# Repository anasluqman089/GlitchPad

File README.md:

# GlitchPad

It is inspire by the movie Matrix 

Matrix rain on a tiny screen, buttons that trigger glitches and sirens, and a real weather sensor hiding inside.

# BOM

1x Seeed Studio XIAO ESP32-S3

4x Cherry MX keyboard

1x Buzzer

1x 220uf resistor

1x LED

1x Rotary Encoder

1x BME280 breakout board

1x O.91 0LED Screen (Blue)

4x M2 screw

4x M3 screw

# Functions

When you turn it on,

It pretends to "boot up" like the Matrix movie and show the text "WAKE UP, NEO..." on the screen with glitchy beeps

When idle,

The screen shows falling Matrix-style rain and every few seconds your room temperature/humidity flickers inside it.

The 4 buttons

1	- Shows "WAKE UP, NEO... THE MATRIX HAS YOU"

2 -	Glitch attack — screen goes crazy + static noise

3 -	Shows real sensor data (temp, humidity, pressure)

4	- Flashing alarm "SYSTEM BREACH" + siren 

The knob

Turn it - adjusts LED brightness

Click it - makes the Matrix rain fall faster

# The Schematic

# The PCB

# The 3D Model

The full model

The lid

The body

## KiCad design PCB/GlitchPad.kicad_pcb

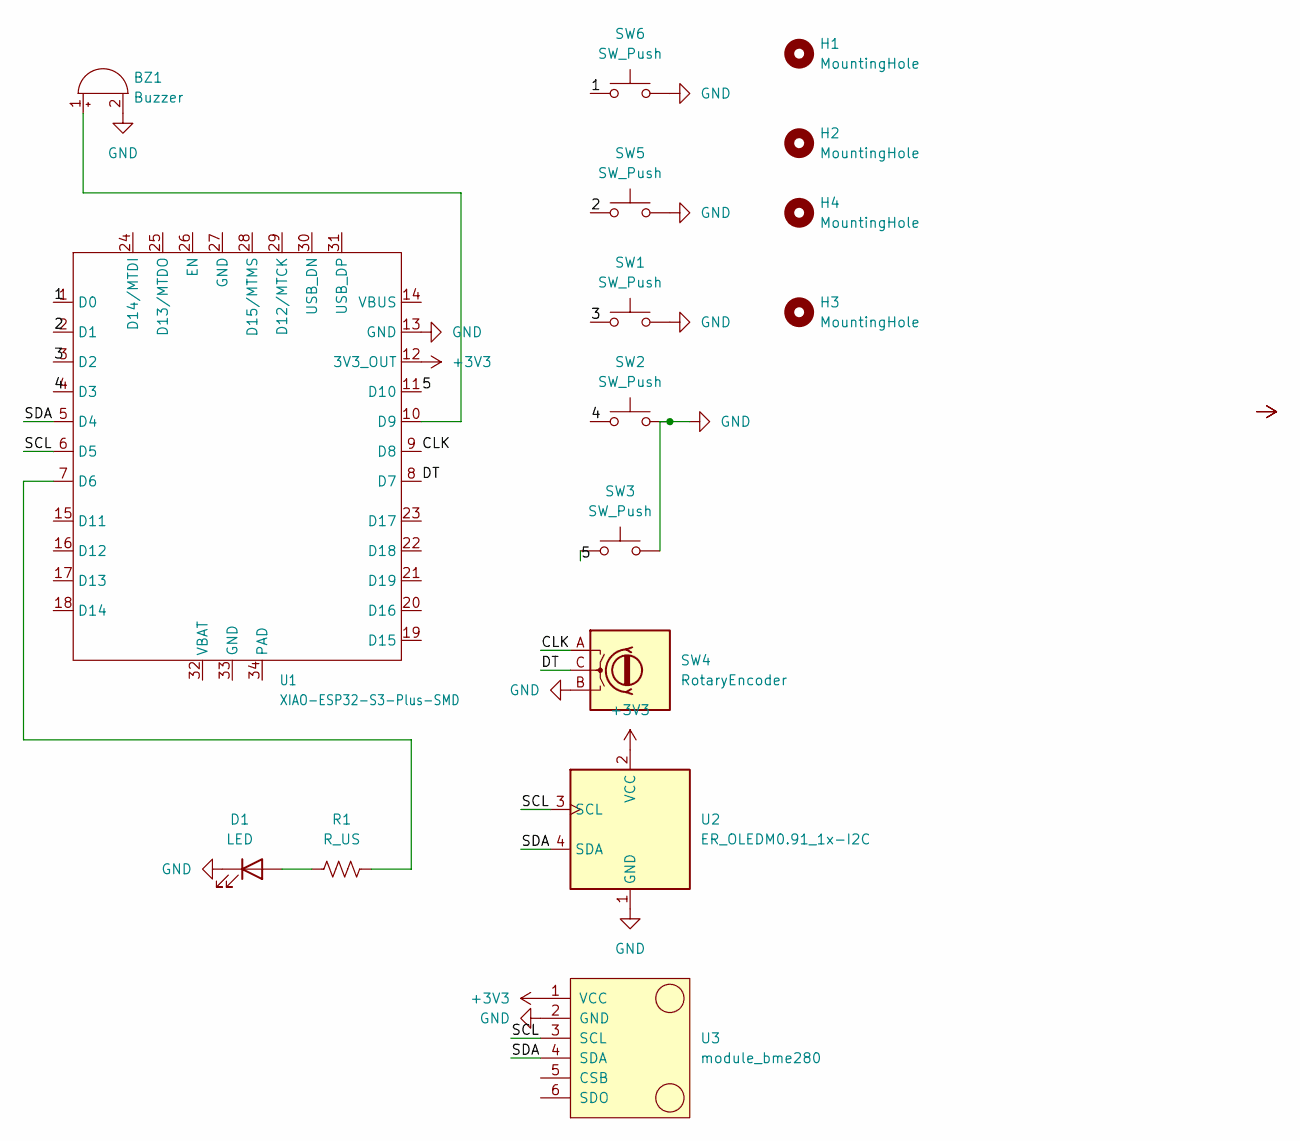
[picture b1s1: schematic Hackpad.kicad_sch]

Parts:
BZ1: Buzzer; Buzzer_12x9.5RM7.6
D1: LED; LED_D5.0mm
H1, H2, H3, H4: MountingHole; MountingHole_2.2mm_M2
R1: R_US; R_Axial_DIN0207_L6.3mm_D2.5mm_P7.62mm_Horizontal
SW1, SW2, SW3, SW5, SW6: SW_Push; SW_Cherry_MX_1.00u_PCB
SW4: RotaryEncoder; RotaryEncoder_Alps_EC11E_Vertical_H20mm
U1: XIAO-ESP32-S3-Plus-SMD; XIAO-ESP32-S3-DIP
U2: ER_OLEDM0.91_1x-I2C
U3: module_bme280

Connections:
+3V3: U1.12 (3V3_OUT), U2.2 (VCC), U3.1 (VCC)
/1: SW6.1, U1.1 (D0)
/2: SW5.1, U1.2 (D1)
/3: SW1.1, U1.3 (D2)
/4: SW2.1, U1.4 (D3)
/5: SW3.1, U1.11 (D10)
/CLK: SW4.A, U1.9 (D8)
/DT: SW4.C, U1.8 (D7)
/SCL: U1.6 (D5), U2.3 (SCL), U3.3 (SCL)
/SDA: U1.5 (D4), U2.4 (SDA), U3.4 (SDA)
GND: BZ1.2 (-), D1.1 (K), SW1.2, SW2.2, SW3.2, SW4.B, SW5.2, SW6.2, U1.13 (GND), U2.1 (GND), U3.2 (GND)
unnamed: BZ1.1 (+), U1.10 (D9)
unnamed: D1.2 (A), R1.1
unnamed: R1.2, U1.7 (D6)

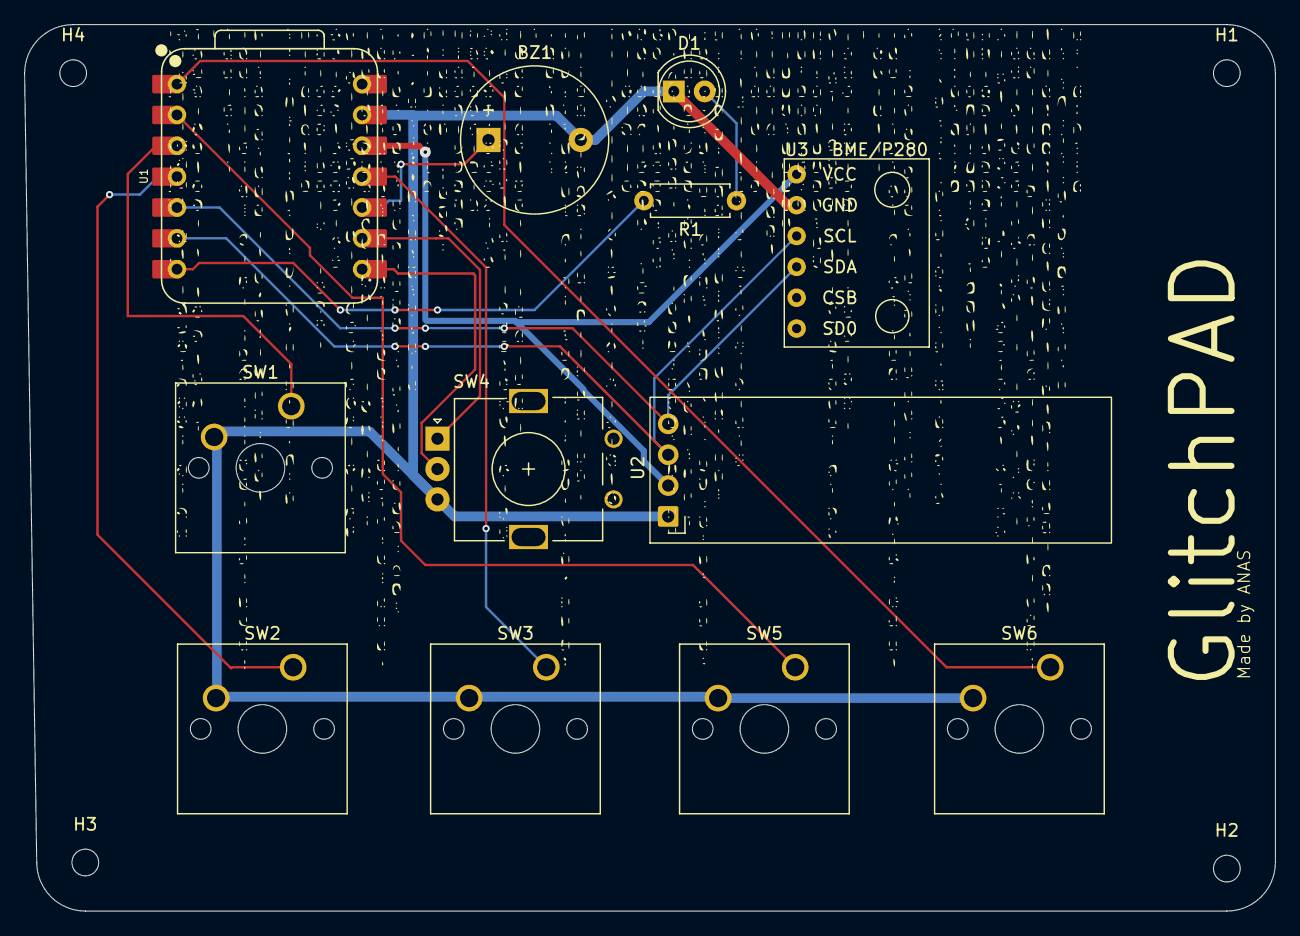
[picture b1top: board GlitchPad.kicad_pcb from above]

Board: 2 copper layers, 103.0 x 73.0 mm, 16 parts (0 on the bottom side), 14 nets.
